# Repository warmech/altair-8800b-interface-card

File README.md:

# Altair 8800B Interface Card
This is a reproduction of the MITS Altair 8800B Interface card, with some cleanup to trace routing and pad placement and an additional quality of life improvement. This card serves as the interface between the Display/Control board and the rest of the 8800B.

This card originally used a staggered ribbon cable terminator that is both expensive and difficult to crimp unless you have the right tools. This version includes a set of two alternative 2x17, 0.1” headers to allow you to use a ribbon cable with female IDC on one end and card-edge on the other. If you cannot locate a pre-fabricated 34-pin cable with these terminators, inexpensive crimping tools are easily found at online retailers that will allow you to build your own cable. The original staggered terminator is crimped and soldered directly to the card PCB and this presented some issues. First, while these are available for sale at retailers such as Mouser and DigiKey, they are around $5.00 per connector (whereas nice, keyed male IDC connectors can be had for a fraction of that), they are not usually stocked in large quantities and may be back-ordered by the time you are assembling this card. Second, these staggered connectors have no stress relief and flexing/bending of the ribbon cables over time will cause the connector to loosen to the extent that signal transmission issues may arise between the interface card and the D/C board. In the case of my and others’ Altairs, this issue caused bus issues that were extremely difficult to hunt down and resolve. Last, if you are assembling your own cables, the staggered connectors require a special insert to crimp; these inserts are neither easy to find nor cheap, so an alternative IDC header offers an inexpensive alternative.

This design is presently untested and I am awaiting a set to be fabricated. Once I have tested this adapter in my 8800B, I will update this disclaimer to indicate as much. Until this disclaimer is updated and/or removed, this PCB is to be strictly treated as experimental only. User beware – these project and fabrication files are provided with absolutely zero guarantees.

For the accompanying CPU, Interface, and Display/Control boards, please see the following repositories:

[Altair 8800B CPU Card](https://github.com/warmech/altair-8800b-cpu-card)

[Altair 8800B Display/Control PCB](https://github.com/warmech/altair-8800b-display-control-pcb)

[Altair 8800B 1702-to-2716/2732 Adapter](https://github.com/warmech/altair-8800b-1702-to-2716-eprom-adapter)

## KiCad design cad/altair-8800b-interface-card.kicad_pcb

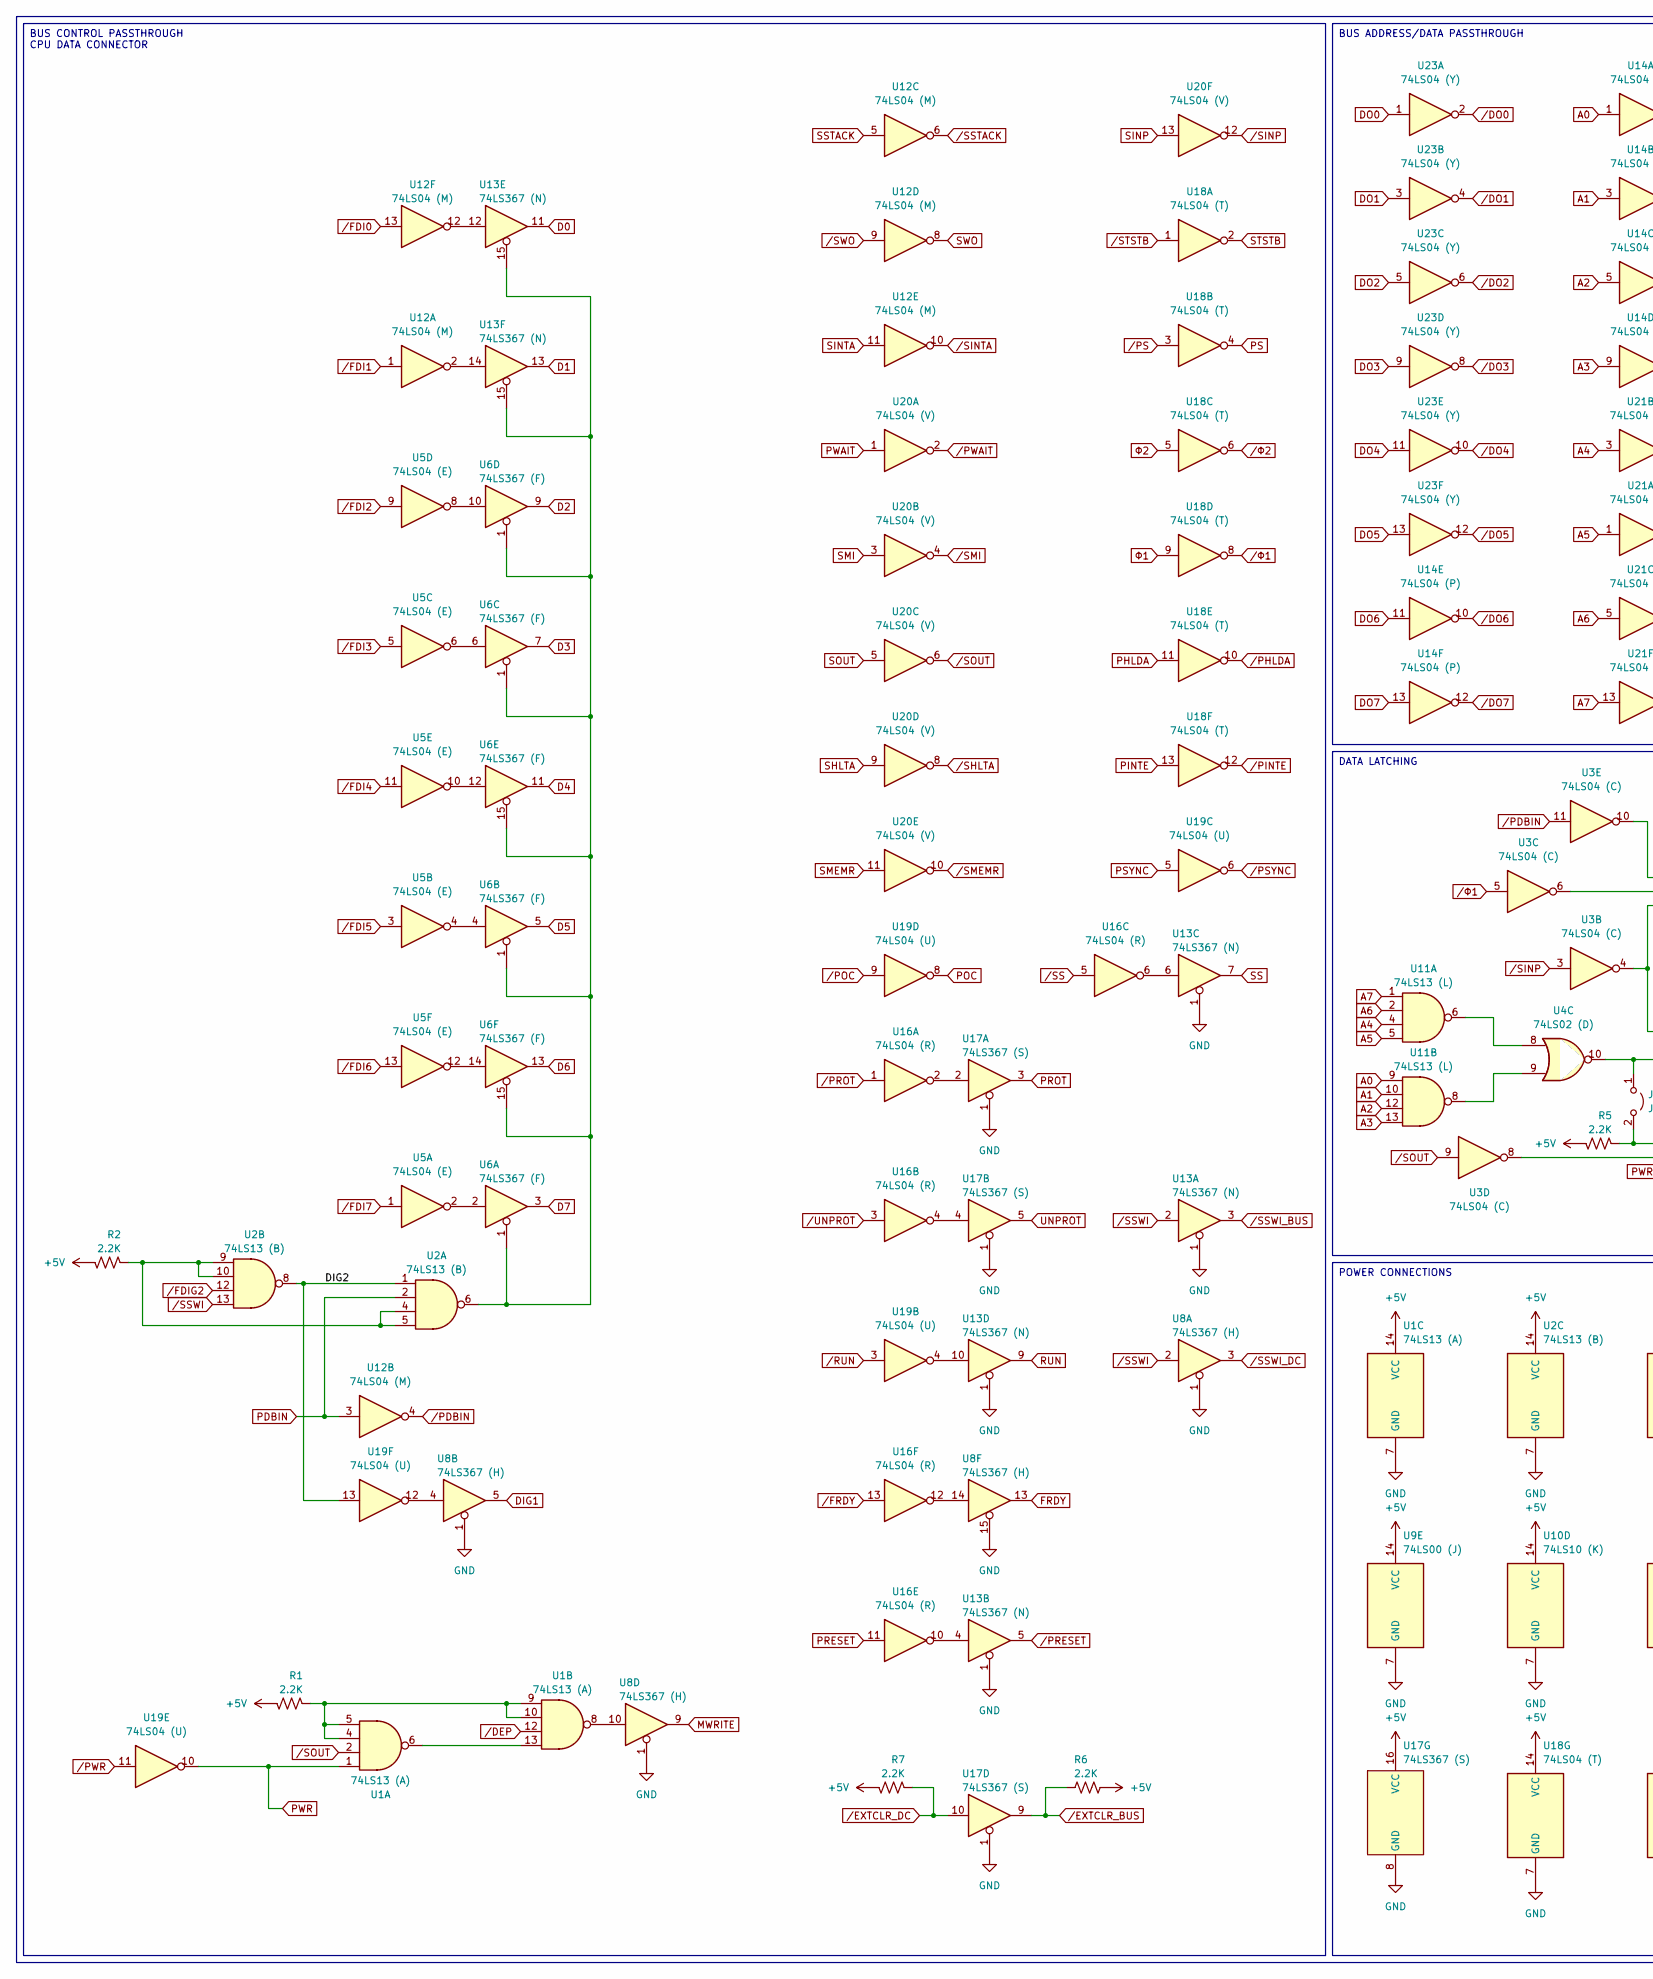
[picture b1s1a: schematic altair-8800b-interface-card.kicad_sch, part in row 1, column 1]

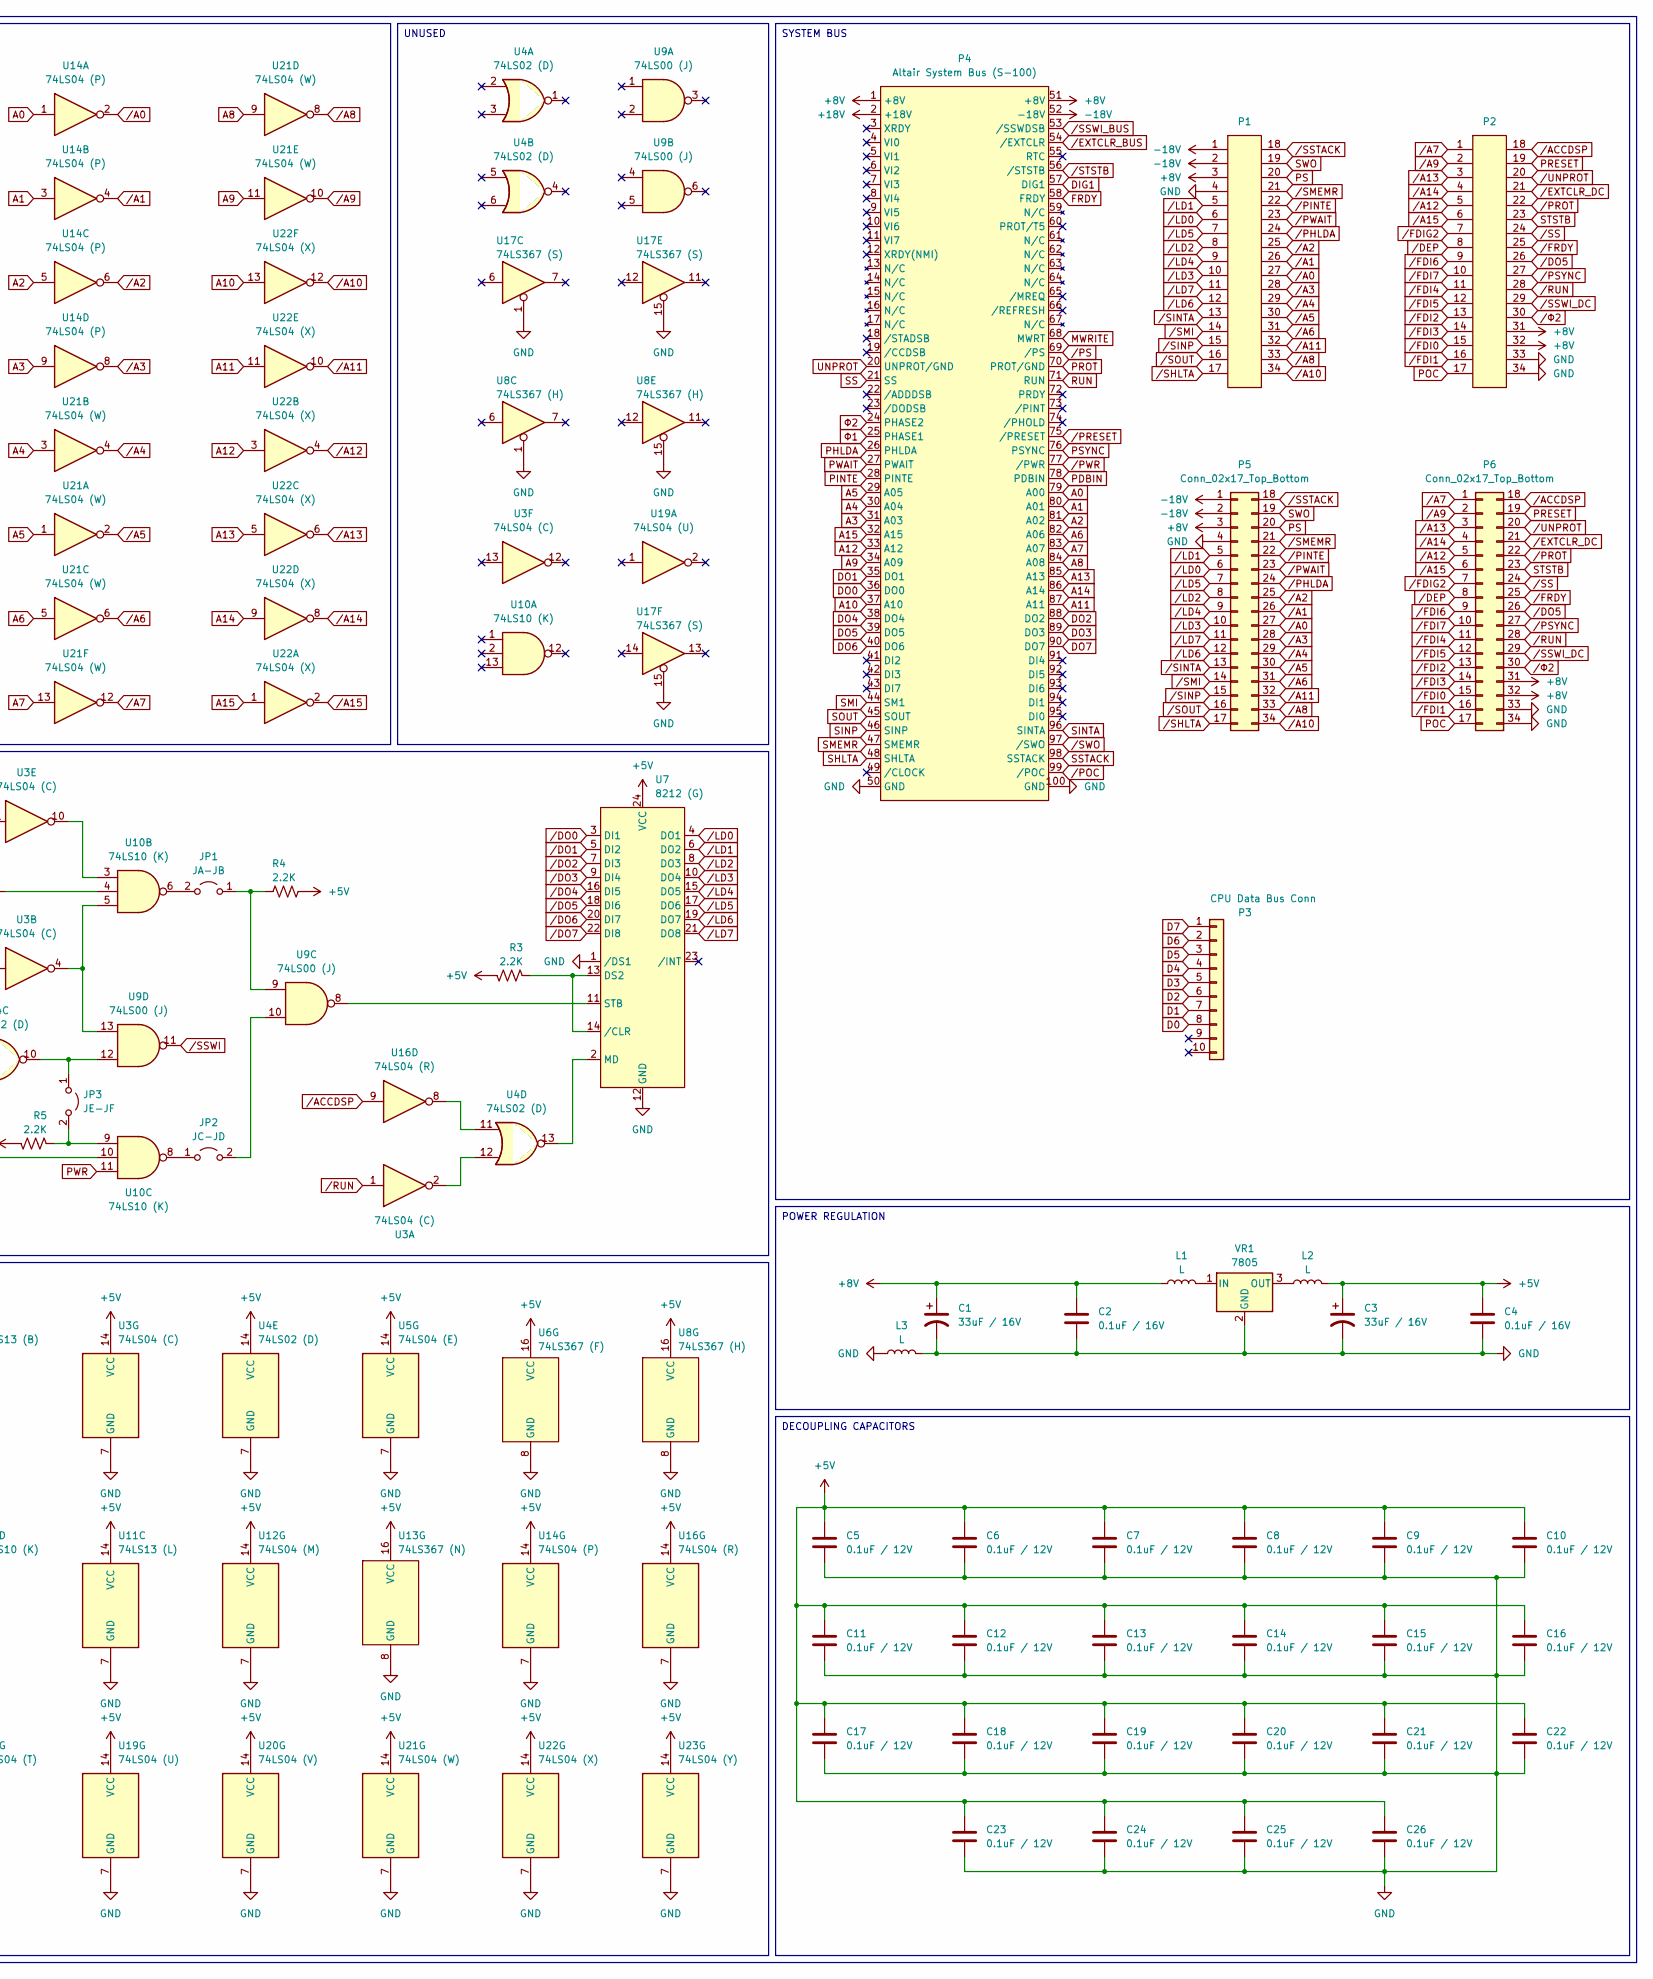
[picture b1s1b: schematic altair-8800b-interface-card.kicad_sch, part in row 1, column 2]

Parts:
C1, C3: 33uF / 16V; CP_Axial_L11.0mm_D5.0mm_P18.00mm_Horizontal
C2, C4: 0.1uF / 16V; C_Disc_D7.0mm_W2.3mm_P5.00mm
C5, C6, C7, C8, C9, C10, C11, C12, C13, C14, C15, C16, C17, C18, C19, C20, C21, C22, C23, C24, C25, C26: 0.1uF / 12V; C_Disc_D7.0mm_W2.3mm_P5.00mm
JP1: JA-JB; PinHeader_1x02_P2.54mm_Vertical
JP2: JC-JD; PinHeader_1x02_P2.54mm_Vertical
JP3: JE-JF; PinHeader_1x02_P2.54mm_Vertical
L1, L2, L3: L; L_Axial_L5.3mm_D2.2mm_P7.62mm_Horizontal_Vishay_IM-1
P1, P2: Ribbon_Cable_Header_PCB_Connector_34_Pin
P3: CPU Data Bus Conn; PinHeader_1x10_P2.54mm_Horizontal
P4: Altair System Bus (S-100); Altair_8800_Bus_Card_Edge
P5, P6: Conn_02x17_Top_Bottom; PinHeader_2x17_P2.54mm_Vertical
R1, R2, R3, R4, R5, R6, R7: 2.2K; R_Axial_DIN0411_L9.9mm_D3.6mm_P12.70mm_Horizontal
U1: 74LS13 (A); DIP-14_W7.62mm_LongPads
U2: 74LS13 (B); DIP-14_W7.62mm_LongPads
U3: 74LS04 (C); DIP-14_W7.62mm_LongPads
U4: 74LS02 (D); DIP-14_W7.62mm_LongPads
U5: 74LS04 (E); DIP-14_W7.62mm_LongPads
U6: 74LS367 (F); DIP-16_W7.62mm_LongPads
U7: 8212 (G); DIP-24_W15.24mm_LongPads
U8: 74LS367 (H); DIP-16_W7.62mm_LongPads
U9: 74LS00 (J); DIP-14_W7.62mm_LongPads
U10: 74LS10 (K); DIP-14_W7.62mm_LongPads
U11: 74LS13 (L); DIP-14_W7.62mm_LongPads
U12: 74LS04 (M); DIP-14_W7.62mm_LongPads
U13: 74LS367 (N); DIP-16_W7.62mm_LongPads
U14: 74LS04 (P); DIP-14_W7.62mm_LongPads
U16: 74LS04 (R); DIP-14_W7.62mm_LongPads
U17: 74LS367 (S); DIP-16_W7.62mm_LongPads
U18: 74LS04 (T); DIP-14_W7.62mm_LongPads
U19: 74LS04 (U); DIP-14_W7.62mm_LongPads
U20: 74LS04 (V); DIP-14_W7.62mm_LongPads
U21: 74LS04 (W); DIP-14_W7.62mm_LongPads
U22: 74LS04 (X); DIP-14_W7.62mm_LongPads
U23: 74LS04 (Y); DIP-14_W7.62mm_LongPads
VR1: 7805; TO-220-3_Horizontal_TabDown

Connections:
+5V: C3.1, C4.1, C5.1, C6.1, C7.1, C8.1, C9.1, C10.1, C11.1, C12.1, C13.1, C14.1, C15.1, C16.1, C17.1, C18.1, C19.1, C20.1, C21.1, C22.1, C23.1, C24.1, C25.1, C26.1, L2.2, R1.1, R2.1, R3.1, R4.1, R5.1, R6.1, R7.1, U1.14 (VCC), U2.14 (VCC), U3.14 (VCC), U4.14 (VCC), U5.14 (VCC), U6.16 (VCC), U7.24 (VCC), U8.16 (VCC), U9.14 (VCC), U10.14 (VCC), U11.14 (VCC), U12.14 (VCC), U13.16 (VCC), U14.14 (VCC), U16.14 (VCC), U17.16 (VCC), U18.14 (VCC), U19.14 (VCC), U20.14 (VCC), U21.14 (VCC), U22.14 (VCC), U23.14 (VCC)
+8V: C1.1, C2.1, L1.1, P1.3, P2.31, P2.32, P4.1 (+8V), P4.51 (+8V), P5.3, P6.31, P6.32
+18V: P4.2 (+18V)
-18V: P1.1, P1.2, P4.52 (-18V), P5.1, P5.2
/DIG2: U2.1, U2.8, U19.13
A0: P4.79 (A00), U11.9, U14.1
A1: P4.80 (A01), U11.10, U14.3
A2: P4.81 (A02), U11.12, U14.5
A3: P4.31 (A03), U11.13, U14.9
A4: P4.30 (A04), U11.4, U21.3
A5: P4.29 (A05), U11.5, U21.1
A6: P4.82 (A06), U11.2, U21.5
A7: P4.83 (A07), U11.1, U21.13
A8: P4.84 (A08), U21.9
A9: P4.34 (A09), U21.11
A10: P4.37 (A10), U22.13
A11: P4.87 (A11), U22.11
A12: P4.33 (A12), U22.3
A13: P4.85 (A13), U22.5
A14: P4.86 (A14), U22.9
A15: P4.32 (A15), U22.1
D0: P3.8, U13.11
D1: P3.7, U13.13
D2: P3.6, U6.9
D3: P3.5, U6.7
D4: P3.4, U6.11
D5: P3.3, U6.5
D6: P3.2, U6.13
D7: P3.1, U6.3
DIG1: P4.57 (DIG1), U8.5
DO0: P4.36 (DO0), U23.1
DO1: P4.35 (DO1), U23.3
DO2: P4.88 (DO2), U23.5
DO3: P4.89 (DO3), U23.9
DO4: P4.38 (DO4), U23.11
DO5: P4.39 (DO5), U23.13
DO6: P4.40 (DO6), U14.11
DO7: P4.90 (DO7), U14.13
FRDY: P4.58 (FRDY), U8.13
GND: C1.2, C2.2, C3.2, C4.2, C5.2, C6.2, C7.2, C8.2, C9.2, C10.2, C11.2, C12.2, C13.2, C14.2, C15.2, C16.2, C17.2, C18.2, C19.2, C20.2, C21.2, C22.2, C23.2, C24.2, C25.2, C26.2, L3.1, L3.2, P1.4, P2.33, P2.34, P4.50 (GND), P4.100 (GND), P5.4, P6.33, P6.34, U1.7 (GND), U2.7 (GND), U3.7 (GND), U4.7 (GND), U5.7 (GND), U6.8 (GND), U7.1 (/DS1), U7.12 (GND), U8.1, U8.8 (GND), U8.15, U9.7 (GND), U10.7 (GND), U11.7 (GND), U12.7 (GND), U13.1, U13.8 (GND), U14.7 (GND), U16.7 (GND), U17.1, U17.8 (GND), U17.15, U18.7 (GND), U19.7 (GND), U20.7 (GND), U21.7 (GND), U22.7 (GND), U23.7 (GND), VR1.2 (GND)
MWRITE: P4.68 (MWRT), U8.9
unnamed: JP1.1 (A), R4.2, U9.9
unnamed: JP1.2 (B), U10.6
unnamed: JP2.1 (A), U10.8
unnamed: JP2.2 (B), U9.10
unnamed: JP3.1 (A), U4.10, U9.12
unnamed: JP3.2 (B), R5.2, U10.9
unnamed: R1.2, U1.4, U1.5, U1.9, U1.10
unnamed: R2.2, U2.4, U2.5, U2.9, U2.10
unnamed: U1.8, U8.10
unnamed: U1.6, U1.13
unnamed: U3.2, U4.12
unnamed: U5.2, U6.2
unnamed: U5.4, U6.4
unnamed: U5.6, U6.6
unnamed: U5.8, U6.10
unnamed: U5.10, U6.12
unnamed: U5.12, U6.14
unnamed: R3.2, U7.13 (DS2), U7.14 (/CLR)
unnamed: U4.13, U7.2 (MD)
unnamed: U7.11 (STB), U9.8
unnamed: U3.10, U10.3
unnamed: U3.6, U10.4
unnamed: U3.4, U9.13, U10.5
unnamed: U3.8, U10.10
unnamed: U4.8, U11.6
unnamed: U4.9, U11.8
unnamed: U12.2, U13.14
unnamed: U12.12, U13.12
unnamed: U13.4, U16.10
unnamed: U13.6, U16.6
unnamed: U13.10, U19.4
unnamed: U2.6, U6.1, U6.15, U13.15
unnamed: U16.2, U17.2
unnamed: U16.4, U17.4
unnamed: U4.11, U16.8
unnamed: U8.14, U16.12
unnamed: U8.4, U19.12
unnamed: L1.2, VR1.1 (IN)
unnamed: L2.1, VR1.3 (OUT)
PDBIN: P4.78 (PDBIN), U2.2, U12.3
PHLDA: P4.26 (PHLDA), U18.11
PINTE: P4.28 (PINTE), U18.13
POC: P2.17, P6.17, U19.8
PRESET: P2.19, P6.19, U16.11
PROT: P4.70 (PROT/GND), U17.3
PS: P1.20, P5.20, U18.4
PSYNC: P4.76 (PSYNC), U19.5
PWAIT: P4.27 (PWAIT), U20.1
PWR: U1.1, U10.11, U19.10
RUN: P4.71 (RUN), U13.9
SHLTA: P4.48 (SHLTA), U20.9
SINP: P4.46 (SINP), U20.13
SINTA: P4.96 (SINTA), U12.11
SMEMR: P4.47 (SMEMR), U20.11
SMI: P4.44 (SM1), U20.3
SOUT: P4.45 (SOUT), U20.5
SS: P4.21 (SS), U13.7
SSTACK: P4.98 (SSTACK), U12.5
STSTB: P2.23, P6.23, U18.2
SWO: P1.19, P5.19, U12.8
UNPROT: P4.20 (UNPROT/GND), U17.5
/A0: P1.27, P5.27, U14.2
/A1: P1.26, P5.26, U14.4
/A2: P1.25, P5.25, U14.6
/A3: P1.28, P5.28, U14.8
/A4: P1.29, P5.29, U21.4
/A5: P1.30, P5.30, U21.2
/A6: P1.31, P5.31, U21.6
/A7: P2.1, P6.1, U21.12
/A8: P1.33, P5.33, U21.8
/A9: P2.2, P6.2, U21.10
/A10: P1.34, P5.34, U22.12
/A11: P1.32, P5.32, U22.10
/A12: P2.5, P6.5, U22.4
/A13: P2.3, P6.3, U22.6
/A14: P2.4, P6.4, U22.8
/A15: P2.6, P6.6, U22.2
/ACCDSP: P2.18, P6.18, U16.9
/DEP: P2.8, P6.8, U1.12
/DO0: U7.3 (DI1), U23.2
/DO1: U7.5 (DI2), U23.4
/DO2: U7.7 (DI3), U23.6
/DO3: U7.9 (DI4), U23.8
/DO4: U7.16 (DI5), U23.10
/DO5: P2.26, P6.26, U7.18 (DI6), U23.12
/DO6: U7.20 (DI7), U14.10
/DO7: U7.22 (DI8), U14.12
/EXTCLR_BUS: P4.54 (/EXTCLR), R6.2, U17.9
/EXTCLR_DC: P2.21, P6.21, R7.2, U17.10
/FDI0: P2.15, P6.15, U12.13
/FDI1: P2.16, P6.16, U12.1
/FDI2: P2.13, P6.13, U5.9
/FDI3: P2.14, P6.14, U5.5
/FDI4: P2.11, P6.11, U5.11
/FDI5: P2.12, P6.12, U5.3
/FDI6: P2.9, P6.9, U5.13
/FDI7: P2.10, P6.10, U5.1
/FDIG2: P2.7, P6.7, U2.12
/FRDY: P2.25, P6.25, U16.13
/LD0: P1.6, P5.6, U7.4 (DO1)
/LD1: P1.5, P5.5, U7.6 (DO2)
/LD2: P1.8, P5.8, U7.8 (DO3)
/LD3: P1.10, P5.10, U7.10 (DO4)
/LD4: P1.9, P5.9, U7.15 (DO5)
/LD5: P1.7, P5.7, U7.17 (DO6)
/LD6: P1.12, P5.12, U7.19 (DO7)
/LD7: P1.11, P5.11, U7.21 (DO8)
/PDBIN: U3.11, U12.4
/PHLDA: P1.24, P5.24, U18.10
/PINTE: P1.22, P5.22, U18.12
/POC: P4.99 (/POC), U19.9
/PRESET: P4.75 (/PRESET), U13.5
/PROT: P2.22, P6.22, U16.1
/PS: P4.69 (/PS), U18.3
/PSYNC: P2.27, P6.27, U19.6
/PWAIT: P1.23, P5.23, U20.2
/PWR: P4.77 (/PWR), U19.11
/RUN: P2.28, P6.28, U3.1, U19.3
/SHLTA: P1.17, P5.17, U20.8
/SINP: P1.15, P5.15, U3.3, U20.12
/SINTA: P1.13, P5.13, U12.10
/SMEMR: P1.21, P5.21, U20.10
/SMI: P1.14, P5.14, U20.4
/SOUT: P1.16, P5.16, U1.2, U3.9, U20.6
/SS: P2.24, P6.24, U16.5
/SSTACK: P1.18, P5.18, U12.6
/SSWI: U2.13, U8.2, U9.11, U13.2
/SSWI_BUS: P4.53 (/SSWDSB), U13.3
/SSWI_DC: P2.29, P6.29, U8.3
/STSTB: P4.56 (/STSTB), U18.1
/SWO: P4.97 (/SWO), U12.9
/UNPROT: P2.20, P6.20, U16.3
/Φ1: U3.5, U18.8
/Φ2: P2.30, P6.30, U18.6
Φ1: P4.25 (PHASE1), U18.9
Φ2: P4.24 (PHASE2), U18.5

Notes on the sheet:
SYSTEM BUS
BUS CONTROL PASSTHROUGH CPU DATA CONNECTOR
DATA LATCHING
POWER REGULATION
POWER CONNECTIONS
UNUSED
DECOUPLING CAPACITORS
BUS ADDRESS/DATA PASSTHROUGH

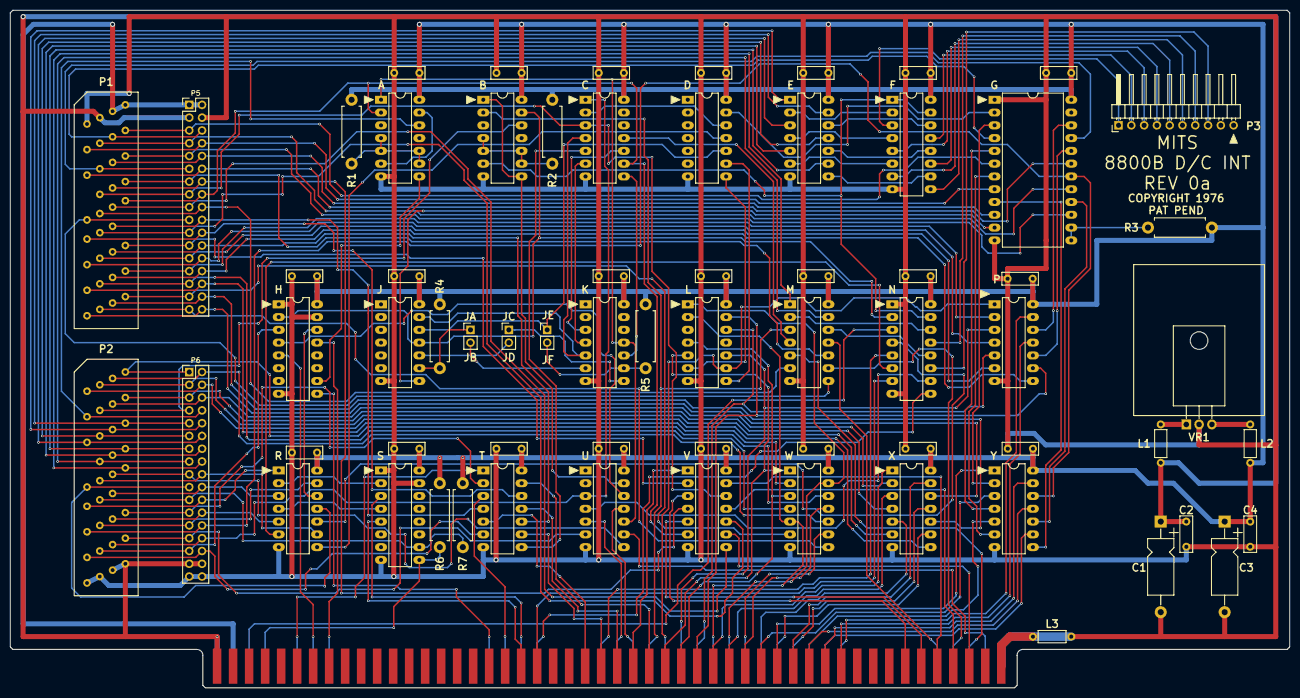
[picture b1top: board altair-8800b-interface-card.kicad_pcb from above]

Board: 2 copper layers, 254.2 x 134.6 mm, 68 parts (0 on the bottom side), 176 nets.

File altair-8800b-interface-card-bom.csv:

Source:,,,,,,,
Date:,9/17/2025 0:42,,,,,,
Tool:,Eeschema 7.0.11-rc3,,,,,,
Generator:,,,,,,,
Component Count:,68,,,,,,
,,,,,,,
Collated Components:,,,,,,,
,,,,,,,
Item,Qty,Reference(s),Value,LibPart,Footprint,Datasheet,DNP
1,2,"C1, C3",33uF / 16V,Device:C_Polarized_US,Capacitor_THT:CP_Axial_L11.0mm_D5.0mm_P18.00mm_Horizontal,~,
2,2,"C2, C4",0.1uF / 16V,Device:C,Capacitor_THT_Custom:C_Disc_D7.0mm_W2.3mm_P5.00mm,~,
3,22,"C5, C6, C7, C8, C9, C10, C11, C12, C13, C14, C15, C16, C17, C18, C19, C20, C21, C22, C23, C24, C25, C26",0.1uF / 12V,Device:C,Capacitor_THT_Custom:C_Disc_D7.0mm_W2.3mm_P5.00mm,~,
4,1,JP1,JA-JB,Jumper:Jumper_2_Open,Connector_PinHeader_2.54mm:PinHeader_1x02_P2.54mm_Vertical,~,
5,1,JP2,JC-JD,Jumper:Jumper_2_Open,Connector_PinHeader_2.54mm:PinHeader_1x02_P2.54mm_Vertical,~,
6,1,JP3,JE-JF,Jumper:Jumper_2_Open,Connector_PinHeader_2.54mm:PinHeader_1x02_P2.54mm_Vertical,~,
7,3,"L1, L2, L3",L,Device:L,Inductor_THT:L_Axial_L5.3mm_D2.2mm_P7.62mm_Horizontal_Vishay_IM-1,~,
8,2,"P1, P2",~,Connector_Custom:Ribbon_Cable_Header_PCB_Connector_34_Pin,Connector_Custom:Ribbon_Cable_Header_PCB_Connector_34_Pin,,
9,1,P3,CPU Data Bus Conn,Connector_Generic:Conn_01x10,Connector_PinHeader_2.54mm:PinHeader_1x10_P2.54mm_Horizontal,~,
10,1,P4,Altair System Bus (S-100),Connector_Custom:MITS_Altair_Bus_CardEdge,Connector_Custom:Altair_8800_Bus_Card_Edge,,
11,2,"P5, P6",Conn_02x17_Top_Bottom,Connector_Generic:Conn_02x17_Top_Bottom,Connector_PinHeader_2.54mm:PinHeader_2x17_P2.54mm_Vertical,~,
12,7,"R1, R2, R3, R4, R5, R6, R7",2.2K,Device:R_US,Resistor_THT:R_Axial_DIN0411_L9.9mm_D3.6mm_P12.70mm_Horizontal,~,
13,1,U1,74LS13 (A),74xx:74LS13,Package_DIP:DIP-14_W7.62mm_LongPads,http://www.ti.com/lit/gpn/sn74LS13,
14,1,U2,74LS13 (B),74xx:74LS13,Package_DIP:DIP-14_W7.62mm_LongPads,http://www.ti.com/lit/gpn/sn74LS13,
15,1,U3,74LS04 (C),74xx:74LS04,Package_DIP:DIP-14_W7.62mm_LongPads,http://www.ti.com/lit/gpn/sn74LS04,
16,1,U4,74LS02 (D),74xx:7402,Package_DIP:DIP-14_W7.62mm_LongPads,http://www.ti.com/lit/gpn/sn7402,
17,1,U5,74LS04 (E),74xx:74LS04,Package_DIP:DIP-14_W7.62mm_LongPads,http://www.ti.com/lit/gpn/sn74LS04,
18,1,U6,74LS367 (F),:74LS367_6,Package_DIP:DIP-16_W7.62mm_LongPads,,
19,1,U7,8212 (G),Interface_Custom:8212,Package_DIP:DIP-24_W15.24mm_LongPads,,
20,1,U8,74LS367 (H),:74LS367_8,Package_DIP:DIP-16_W7.62mm_LongPads,,
21,1,U9,74LS00 (J),74xx:7400,Package_DIP:DIP-14_W7.62mm_LongPads,http://www.ti.com/lit/gpn/sn7400,
22,1,U10,74LS10 (K),74xx:74LS10,Package_DIP:DIP-14_W7.62mm_LongPads,http://www.ti.com/lit/gpn/sn74LS10,
23,1,U11,74LS13 (L),74xx:74LS13,Package_DIP:DIP-14_W7.62mm_LongPads,http://www.ti.com/lit/gpn/sn74LS13,
24,1,U12,74LS04 (M),74xx:74LS04,Package_DIP:DIP-14_W7.62mm_LongPads,http://www.ti.com/lit/gpn/sn74LS04,
25,1,U13,74LS367 (N),:74LS367_20,Package_DIP:DIP-16_W7.62mm_LongPads,,
26,1,U14,74LS04 (P),74xx:74LS04,Package_DIP:DIP-14_W7.62mm_LongPads,http://www.ti.com/lit/gpn/sn74LS04,
27,1,U16,74LS04 (R),74xx:74LS04,Package_DIP:DIP-14_W7.62mm_LongPads,http://www.ti.com/lit/gpn/sn74LS04,
28,1,U17,74LS367 (S),:74LS367_26,Package_DIP:DIP-16_W7.62mm_LongPads,,
29,1,U18,74LS04 (T),74xx:74LS04,Package_DIP:DIP-14_W7.62mm_LongPads,http://www.ti.com/lit/gpn/sn74LS04,
30,1,U19,74LS04 (U),74xx:74LS04,Package_DIP:DIP-14_W7.62mm_LongPads,http://www.ti.com/lit/gpn/sn74LS04,
31,1,U20,74LS04 (V),74xx:74LS04,Package_DIP:DIP-14_W7.62mm_LongPads,http://www.ti.com/lit/gpn/sn74LS04,
32,1,U21,74LS04 (W),74xx:74LS04,Package_DIP:DIP-14_W7.62mm_LongPads,http://www.ti.com/lit/gpn/sn74LS04,
33,1,U22,74LS04 (X),74xx:74LS04,Package_DIP:DIP-14_W7.62mm_LongPads,http://www.ti.com/lit/gpn/sn74LS04,
34,1,U23,74LS04 (Y),74xx:74LS04,Package_DIP:DIP-14_W7.62mm_LongPads,http://www.ti.com/lit/gpn/sn74LS04,
35,1,VR1,7805,Regulator_Linear:L7805,Package_TO_SOT_THT:TO-220-3_Horizontal_TabDown,http://www.st.com/content/ccc/resource/technical/document/da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,

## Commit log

2025-10-20 Removed junk metadata files from project

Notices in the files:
cad/altair-8800b-interface-card.kicad_pcb:
COPYRIGHT 1976
